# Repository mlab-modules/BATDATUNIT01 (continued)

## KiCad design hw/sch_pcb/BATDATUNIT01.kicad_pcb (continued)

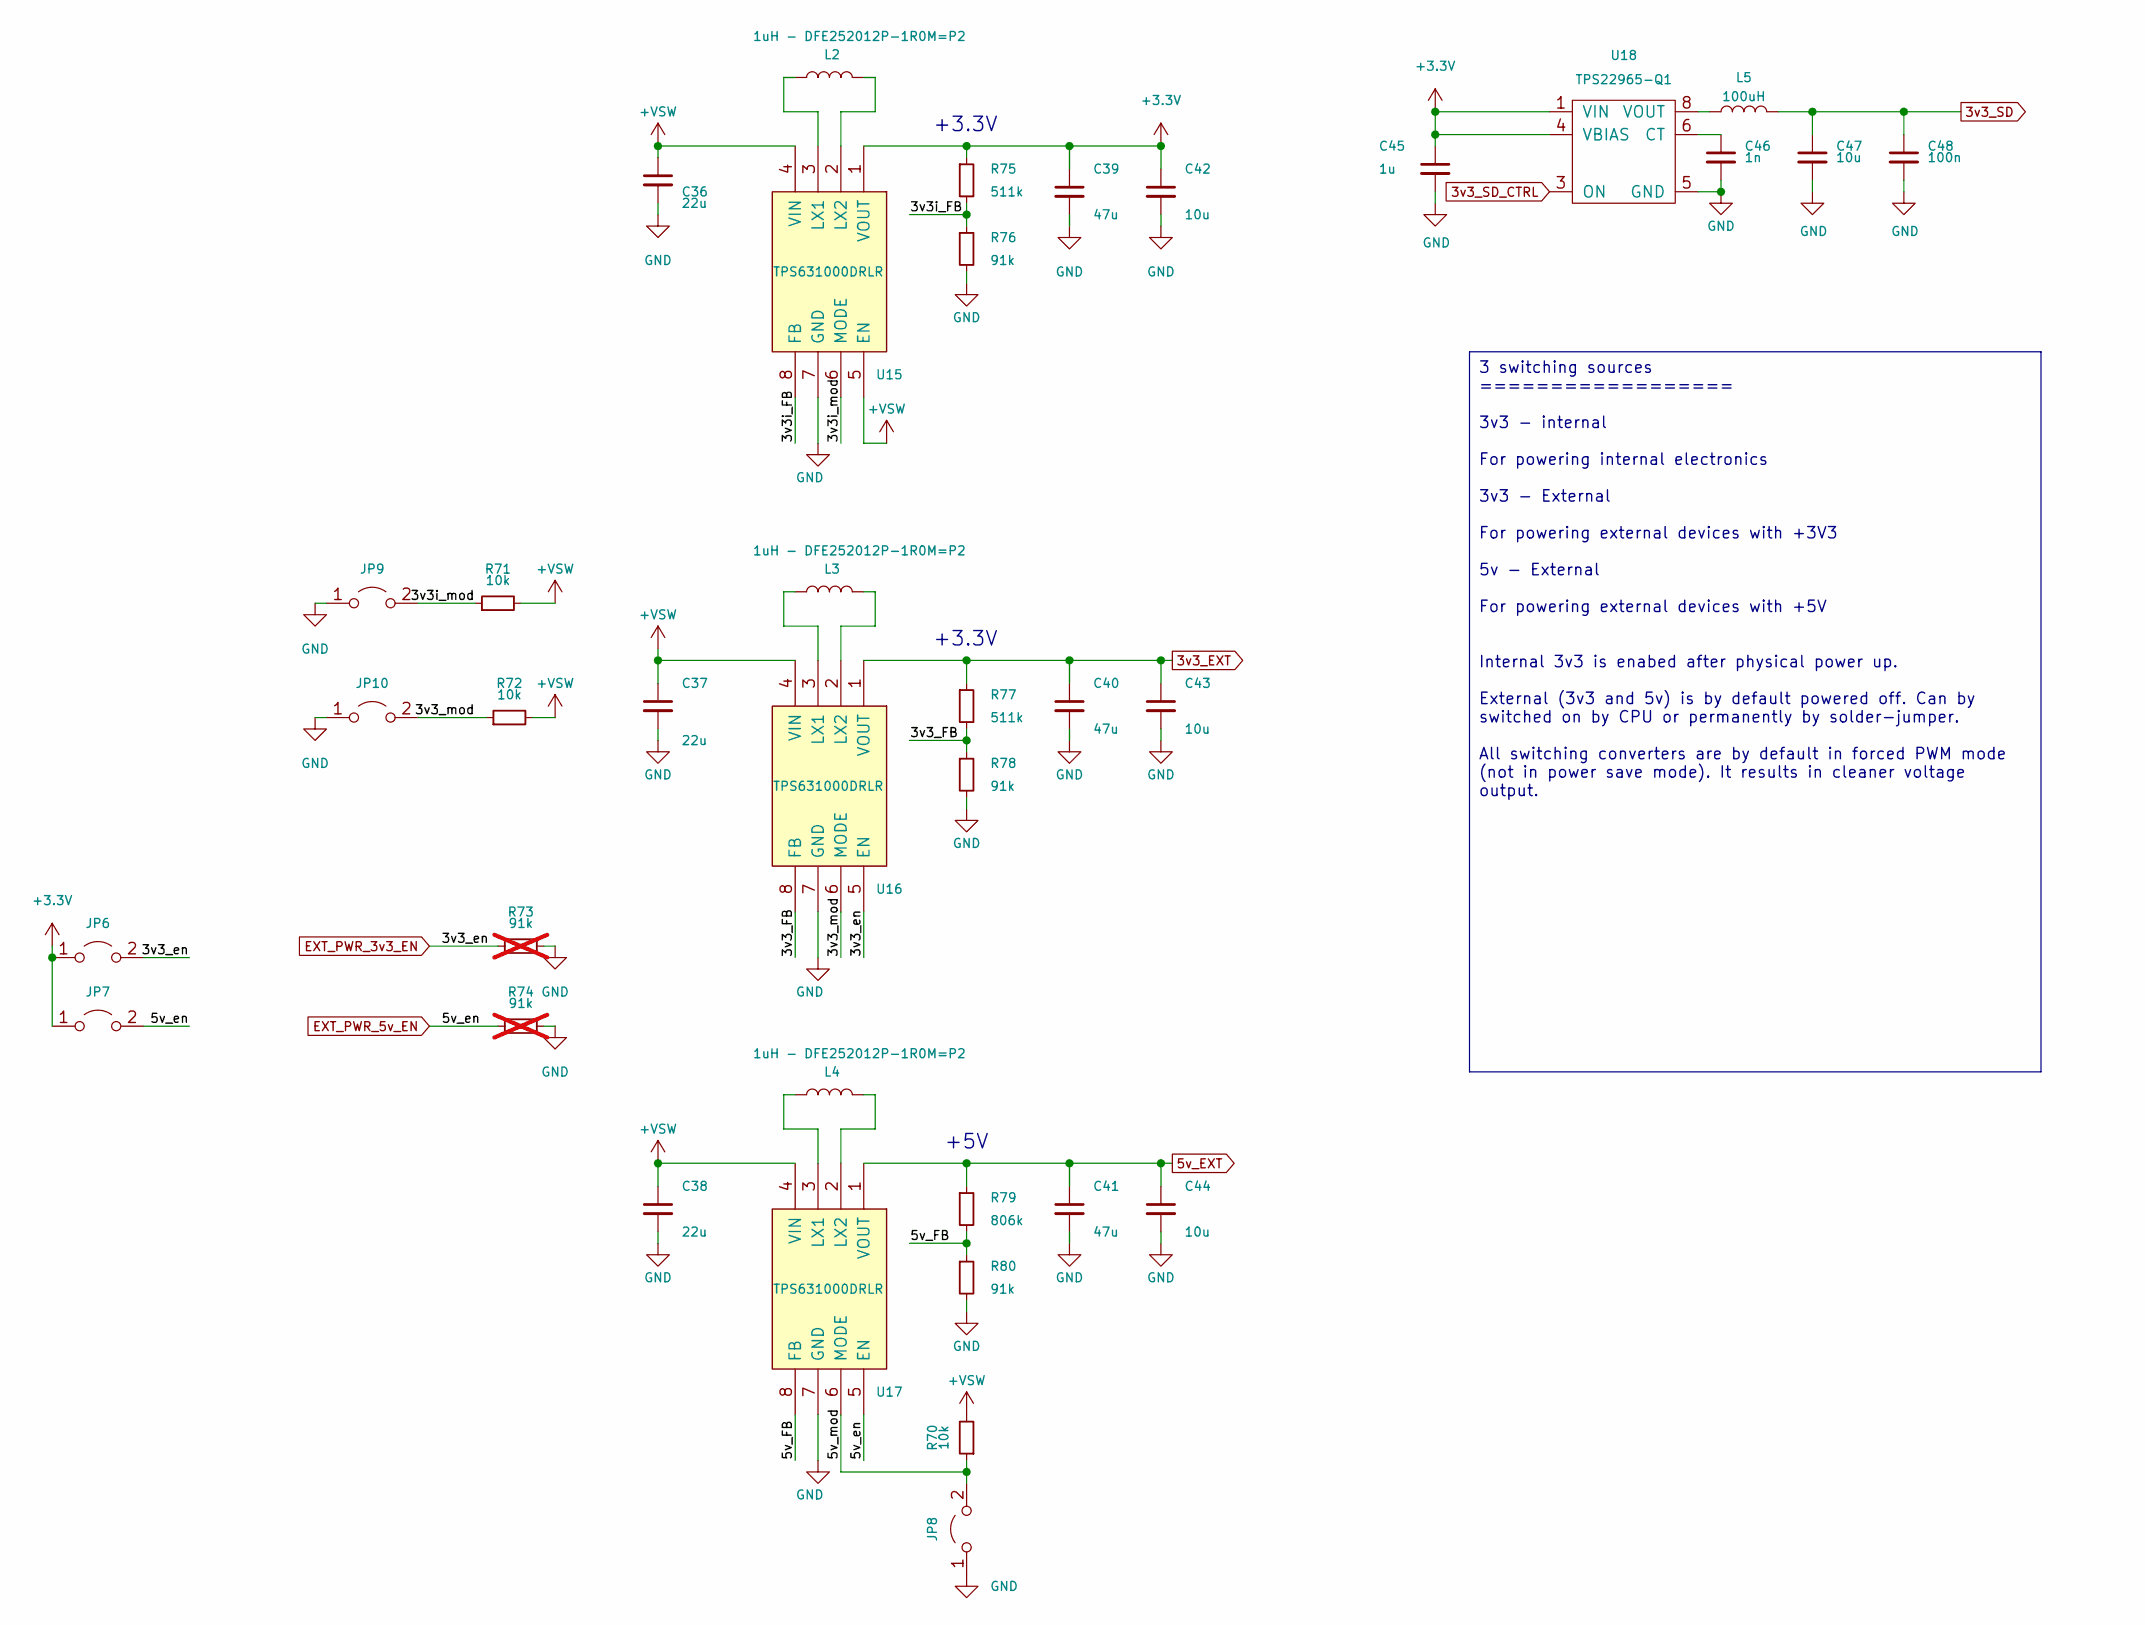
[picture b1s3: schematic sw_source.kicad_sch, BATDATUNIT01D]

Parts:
C36, C37, C38: 22u; C_0805_2012Metric
C39, C40, C41: 47u; C_0805_2012Metric
C42, C43, C44, C47: 10u; C_0805_2012Metric
C45: 1u; C_0805_2012Metric
C46: 1n; C_0805_2012Metric
C48: 100n; C_0805_2012Metric
JP6, JP7, JP8, JP9, JP10: Jumper_2_Open; SolderJumper-2_P1.3mm_Open_RoundedPad1.0x1.5mm
L2, L3, L4: 1uH - DFE252012P-1R0M=P2; L_1008_2520Metric
L5: 100uH; L_0805_2012Metric_Pad1.15x1.40mm_HandSolder
R70, R71, R72: 10k; R_0805_2012Metric
R73, R74: 91k; R_0805_2012Metric; not fitted
R75, R77: 511k; R_0805_2012Metric
R76, R78, R80: 91k; R_0805_2012Metric
R79: 806k; R_0805_2012Metric
U15, U16, U17: TPS631000DRLR; SOT-583-8; Mouser Part Number 595-TPS631000DRLR
U18: TPS22965-Q1; WSON-8-1EP_2x2mm_P0.5mm_EP0.9x1.6mm

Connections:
3v3_EXT: C40.1, C43.1, R77.1, U16.1 (VOUT); also elsewhere on the board
3v3_SD: C47.1, C48.1, L5.2; also elsewhere on the board
3v3_SD_CTRL: U18.3 (ON); also elsewhere on the board
5v_EXT: C41.1, C44.1, R79.1, U17.1 (VOUT); also elsewhere on the board
+3.3V: C39.1, C42.1, C45.1, JP6.1 (A), JP7.1 (A), R75.1, U15.1 (VOUT), U18.1 (VIN), U18.2 (VIN), U18.4 (VBIAS); also elsewhere on the board
+VSW: C36.1, C37.1, C38.1, R70.2, R71.2, R72.2, U15.4 (VIN), U15.5 (EN), U16.4 (VIN), U17.4 (VIN); also elsewhere on the board
/sw_source/3v3_FB: R77.2, R78.1, U16.8 (FB)
/sw_source/3v3_mod: JP10.2 (B), R72.1, U16.6 (MODE)
/sw_source/3v3i_FB: R75.2, R76.1, U15.8 (FB)
/sw_source/3v3i_mod: JP9.2 (B), R71.1, U15.6 (MODE)
/sw_source/5v_FB: R79.2, R80.1, U17.8 (FB)
/sw_source/5v_mod: JP8.2 (B), R70.1, U17.6 (MODE)
EXT_PWR_3v3_EN: JP6.2 (B), R73.2, U16.5 (EN); also elsewhere on the board
EXT_PWR_5v_EN: JP7.2 (B), R74.2, U17.5 (EN); also elsewhere on the board
GND: C36.2, C37.2, C38.2, C39.2, C40.2, C41.2, C42.2, C43.2, C44.2, C45.2, C46.2, C47.2, C48.2, JP8.1 (A), JP9.1 (A), JP10.1 (A), R73.1, R74.1, R76.2, R78.2, R80.2, U15.7 (GND), U16.7 (GND), U17.7 (GND), U18.5 (GND), U18.9; also elsewhere on the board
unnamed: L5.1, U18.7 (VOUT), U18.8 (VOUT)
unnamed: L2.1, U15.3 (LX1)
unnamed: L2.2, U15.2 (LX2)
unnamed: L3.1, U16.3 (LX1)
unnamed: L3.2, U16.2 (LX2)
unnamed: L4.1, U17.3 (LX1)
unnamed: L4.2, U17.2 (LX2)
unnamed: C46.1, U18.6 (CT)

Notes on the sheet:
+3.3V
+5V
3 switching sources ================== 3v3 - internal For powering internal electronics 3v3 - External For powering external devices with +3V3 5v - External For powering external devices with +5V Internal 3v3 is enabed after physical power up. External (3v3 and 5v) is by default powered off. Can by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

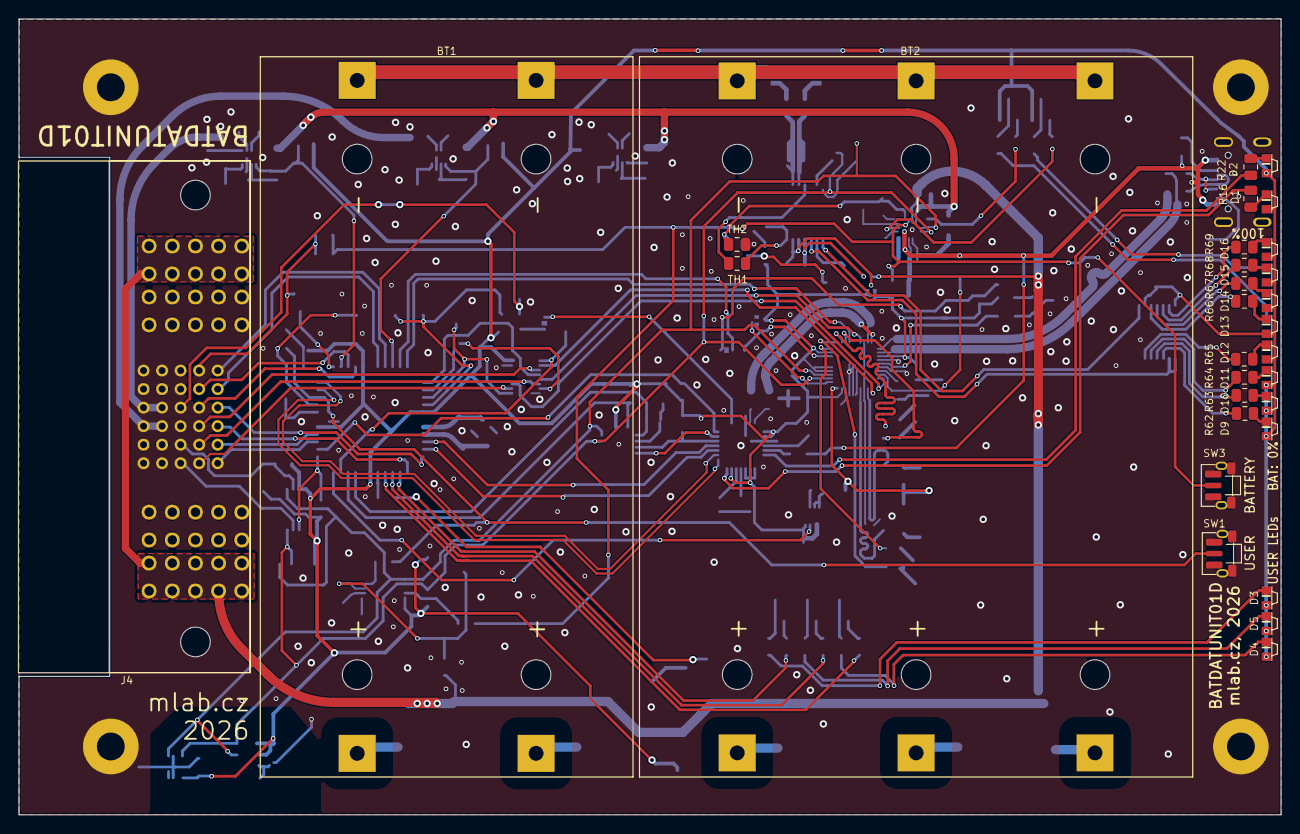
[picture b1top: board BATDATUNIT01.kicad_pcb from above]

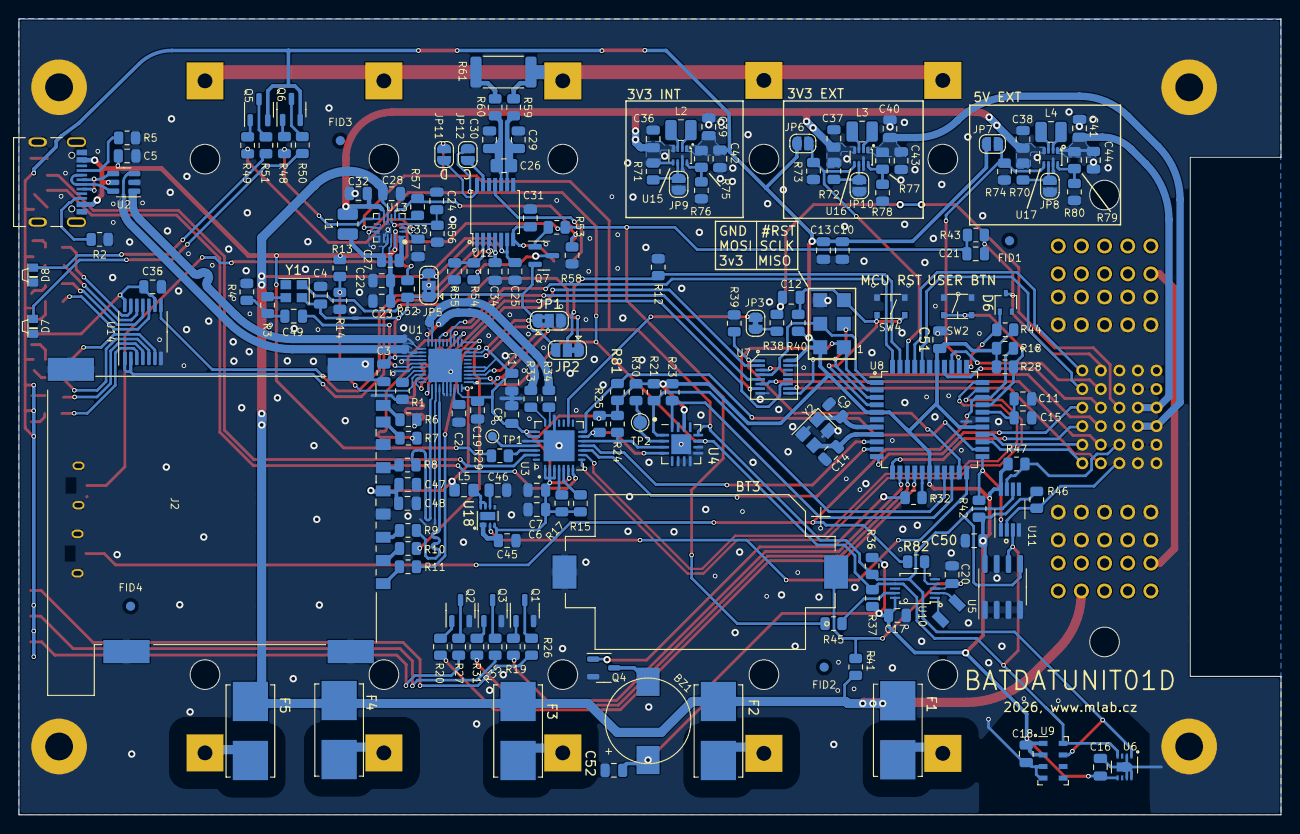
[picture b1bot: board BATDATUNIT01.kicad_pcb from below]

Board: 2 copper layers, 136.2 x 85.9 mm, 225 parts (191 on the bottom side), 182 nets.

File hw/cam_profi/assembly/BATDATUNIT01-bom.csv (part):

Component,Description,Part,References,Value,Footprint,Quantity Per PCB,Datasheet,ust_id,mfpn,mpn,sim.device,sim.type,sim.pins,height,i2c,manufacturer_name,manufacturer_part_number,mouser part number,mouser price/stock,arrow part number,arrow price/stock,lcsc
1,Single-cell battery,2xBATT,BT1,BATT,BAT_BK-18650-PC4,1,~,5c70984412875079b91f87e9,,,,,,,,,,,,,,
2,Single-cell battery,3xBATT,BT2,BATT,BAT_BK-18650-PC6,1,~,63567f66c8e7b5bbef872ce1,,,,,,,,,,,,,,
3,Single-cell battery,Battery_Cell,BT3,CR2032,BatteryHolder_Keystone_1060_1x2032,1,~,68249eacee7fc534862c6977,,,,,,,,,,,,,,
4,"Buzzer, polarized",Buzzer,BZ1,LET9032ES-03L,MagneticBuzzer_LET9032ES-03L-2.7-16-R,1,https://www.cre-soundbuzzer.com/datasheet/LET9032ES-03L-2.7-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,5fa0f13812875025b3977890,,,,,,,,,,,,,,
5,"Unpolarized capacitor, small symbol",C_Small,C9C14,15p,C_0805_2012Metric,2,~,5c70984712875079b91f8b32,,,,,,,,,,,,,,
6,"Unpolarized capacitor, small symbol",C_Small,C5C46,1n,C_0805_2012Metric,2,~,5c70984712875079b91f8b45,C0805 1u,C0805 1u,,,,,,,,,,,,
7,"Unpolarized capacitor, small symbol",C_Small,C34,3n3,C_0805_2012Metric,1,~,5c70984712875079b91f8b47,,,,,,,,,,,,,,
8,"Unpolarized capacitor, small symbol",C_Small,C27,47n,C_0805_2012Metric,1,~,65482046462c6d9e72056b98,,,,,,,,,,,,,,
9,"Unpolarized capacitor, small symbol",C_Small,C1C2C3C4C6C8C10C13C15C16C17C18C20C23C25C26C29C30C35C48C49C50C51C52,100n,C_0805_2012Metric,24,~,5c70984712875079b91f8b4c,,,,,,,,,,,,,,
10,"Unpolarized capacitor, small symbol",C_Small,C19C24C31C45,1u,C_0805_2012Metric,4,~,5c70984712875079b91f8b50,,,,,,,,,,,,,,
11,"Unpolarized capacitor, small symbol",C_Small,C7C12C33,4u7,C_0805_2012Metric,3,~,5c70984712875079b91f8b52,,,,,,,,,,,,,,
12,"Unpolarized capacitor, small symbol",C_Small,C11C22C28C42C43C44C47,10u,C_0805_2012Metric,7,~,5c70984712875079b91f8b53,,,,,,,,,,,,,,
13,"Unpolarized capacitor, small symbol",C_Small,C21C32C36C37C38,22u,C_0805_2012Metric,5,~,650b58f1462c6d9e7205463b,,,,,,,,,,,,,,
14,"Unpolarized capacitor, small symbol",C_Small,C39C40C41,47u,C_0805_2012Metric,3,~,5c70984812875079b91f8bbf,,,,,,,,,,,,,,
15,"100V, 0.175A, High-speed Switching Diode, SOT-323",BAS16W,D6,BAS16W,SOT-323_SC-70,1,https://assets.nexperia.com/documents/data-sheet/BAS16_SER.pdf,5c70984512875079b91f88af,,,,,,,,,,,,,,
16,"Light emitting diode, small symbol",LED_Small,D3D8D13D14D15D16,GREEN,SMD_LED_RIGHT_KINGBRIGHT_1605,6,~,65481f0c462c6d9e72056b3d,,,,,,,,,,,,,,
17,Light emitting diode,LED,D2,GREEN,SMD_LED_RIGHT_KINGBRIGHT_1605,1,https://cz.mouser.com/datasheet/2/216/APA1606SGC-76546.pdf,65481f0c462c6d9e72056b3d,,,,,,,,,,,,,,
18,"Light emitting diode, small symbol",LED_Small,D4D7D11D12,ORANGE,SMD_LED_RIGHT_KINGBRIGHT_1605,4,~,65481fdd462c6d9e72056b6a,,,,,,,,,,,,,,
19,Light emitting diode,LED,D1,RED,SMD_LED_RIGHT_KINGBRIGHT_1605,1,https://cz.mouser.com/datasheet/2/216/APA1606SURCK-63848.pdf,65481f96462c6d9e72056b54,,,,,,,,,,,,,,
20,"Light emitting diode, small symbol",LED_Small,D5D9D10,RED,SMD_LED_RIGHT_KINGBRIGHT_1605,3,~,65481f96462c6d9e72056b54,,,,,,,,,,,,,,
21,Fuse,Fuse,F1F2F3F4F5,Fuse,Fuseholder_Littelfuse_Nano2_154x,5,https://cz.mouser.com/datasheet/2/240/media-3321028.pdf,5c70984512875079b91f88d8,,,,,,,,,,,,,,
22,,MOLEX_46436-9327,J4,46436-9327,MOLEX_46436-9327,1,,65481d4a462c6d9e72056b06,,,,,,,,,,,,,,
23,2x03 2.54 mm pitch header,HEADER_2x03,J3,HEADER_2x03,SMD_2x03,1,,x,,,,,,,,,,,,,,
24,,SD_Card-FPS009-4200-0,J2,SD_Card-FPS009-4200-0,FPS009-4200-0,1,,5cdd24d5128750448edda353,,,,,,,,,,,,,,
25,USB 2.0-only Type-C Receptacle connector,USBC_USB4105-GF-A,J1,USBC_USB4105-GF-A,USBC GCT_USB4105-GF-A,1,,5fa0f94612875025b397795e,USB4105-GF-A,USB4105-GF-A,,,,,,,,,,,,
26,"Jumper, 2-pole, open",Jumper_2_Open,JP6JP7JP8JP9JP10JP11JP12,Jumper_2_Open,SolderJumper-2_P1.3mm_Open_RoundedPad1.0x1.5mm,7,~,x,,,,,,,,,,,,,,
27,Inductor,L,L5,100uH,L_0805_2012Metric_Pad1.15x1.40mm_HandSolder,1,~,626fd6fcdc56076e9a222966,,,,,,,,,,,,,,
28,Inductor,L,L1L2L3L4,1uH - DFE252012P-1R0M=P2,L_1008_2520Metric,4,~,650b5977462c6d9e72054656,,,,,,,,,,,,,,
29,"PNP transistor, base/emitter/collector",Q_PNP_BEC,Q5Q6,BC807-25,SOT-23-3,2,~,5c70984712875079b91f8aeb,,,NPN,GUMMELPOON,1=C 2=B 3=E,,,,,,,,,
30,"NPN transistor, base/emitter/collector",Q_NPN_BEC,Q1Q2Q3Q4,BC817-25,SOT-23-3,4,~,5c70984712875079b91f8aea,,,NPN,GUMMELPOON,1=C 2=B 3=E,,,,,,,,,
31,"P-MOSFET transistor, gate/source/drain",Q_PMOS_GSD,Q7,BSS83P,SOT-23,1,~,5c70984712875079b91f8ae6,,,,,,,,,,,,,,
32,"Resistor, small symbol",R_Small,R33R34,33R,R_0805_2012Metric,2,~,5c70984512875079b91f8970,,,,,,,,,,,,,,
33,"Resistor, small symbol",R_Small,R22R26R51R66R67R68R69,68R,R_0805_2012Metric,7,~,5c70984512875079b91f8975,,,,,,,,,,,,,,
34,,R-device-DATALOGGER01A-rescue-CCP2019V01A-rescue-SPACEDOS01A_PCB01A-rescue-SPACEDOS01B_PCB01A-rescue,R6R7R8R9R10R11R38R82,100R,R_0805_2012Metric,8,,5c70984512875079b91f8977,,,,,,,,,,,,,,
35,"Resistor, small symbol",R_Small,R59R60,100R,R_0805_2012Metric,2,~,5c70984512875079b91f8977,,,,,,,,,,,,,,
36,"Resistor, small symbol",R_Small,R16R27R35R50R54R62R63R64R65,270R,R_0805_2012Metric,9,~,5c70984512875079b91f8983,,,,,,,,,,,,,,
37,"Resistor, small symbol",R_Small,R53,510R,R_0805_2012Metric,1,~,5c70984512875079b91f8988,,,,,,,,,,,,,,
38,"Resistor, small symbol",R_Small,R15R17R19R20R31R32R48R49R55,1k,R_0805_2012Metric,9,~,5c70984512875079b91f898c,,,,,,,,,,,,,,
39,"Resistor, small symbol",R_Small,R56,2k4,R_0805_2012Metric,1,~,5c70984612875079b91f8991,,,,,,,,,,,,,,
40,"Resistor, small symbol",R_Small,R2R4R5R29R57,5k1,R_0805_2012Metric,5,~,5fa0fc3e12875025b3977997,,,,,,,,,,,,,,
41,"Resistor, small symbol",R_Small,R1,6.19k,R_0805_2012Metric,1,~,6548142e462c6d9e72056976,,,,,,,,,,,,,,
42,"Resistor, small symbol",R_Small,R3R18R21R23R24R25R28R30R36R37R40R42R44R46R47R70R72R81,10k,R_0805_2012Metric,18,~,5c70984612875079b91f899f,,,,,,,,,,,,,,
43,"Resistor, small symbol",R_Small,R14,25k5,R_0805_2012Metric,1,~,5c70984712875079b91f8a88,,,,,,,,,,,,,,
44,"Resistor, small symbol",R_Small,R58,33k,R_0805_2012Metric,1,~,5c70984712875079b91f8a8a,,,,,,,,,,,,,,
45,"Resistor, small symbol",R_Small,R13,68k,R_0805_2012Metric,1,~,5c70984712875079b91f8a91,,,,,,,,,,,,,,
46,"Resistor, small symbol",R_Small,R76R78R80,91k,R_0805_2012Metric,3,~,5c70984712875079b91f8a95,,,,,,,,,,,,,,
47,"Resistor, small symbol",R_Small,R43,270k,R_0805_2012Metric,1,~,5c70984712875079b91f8aa0,,,,,,,,,,,,,,
48,"Resistor, small symbol",R_Small,R75R77,511k,R_0805_2012Metric,2,~,650b5a43462c6d9e7205468e,,,,,,,,,,,,,,
49,"Resistor, small symbol",R_Small,R79,806k,R_0805_2012Metric,1,~,650b5abb462c6d9e720546b8,,,,,,,,,,,,,,
50,"Resistor, small symbol",R_Small,R61,0R01 75PPM,R_2512_6332Metric,1,~,5c70984712875079b91f8abf,,,,,,,,,,,,,,
51,"Push button switch, generic, two pins",SW_Push,SW2SW4,KMT031,KMT031 NGJ LHS C&K,2,~,612515a61287500165a9771d,,,,,,,,,,,,,,
52,"Push button switch, generic, two pins",SW_Push_shield,SW1SW3,SKRTLAE010,SKRT,2,~,65481517462c6d9e720569b4,,,,,,,,,,,,,,
53,Temperature dependent resistor,Thermistor,TH1,10k NTC,R_0805_2012Metric,1,~,5c70984712875079b91f8ac5,,,,,,,,,,,,,,
54,"Temperature dependent resistor, negative temperature coefficient",Thermistor_NTC,TH2,10k NTC,R_0805_2012Metric,1,~,5c70984712875079b91f8ac5,,,,,,,,,,,,,,
55,"I2C Serial EEPROM, 64Kb (8192x8) with Unique Serial Number, SO8",AT24CS64-SSHM,U5,AT24CS64-SSHM,SOIC-8_3.9x4.9mm_P1.27mm,1,http://ww1.microchip.com/downloads/en/DeviceDoc/Atmel-8870-S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,5c70984712875079b91f8b99,,,,,,1.5,,,,,,,,
56,"20MHz, 128kB Flash, 16kB SRAM, 4kB EEPROM, JTAG, TQFP-44",ATmega1284P-A,U8,ATMEGA1284P-AU,TQFP-44_10x10mm_P0.8mm,1,http://www.atmel.com/Images/Atmel-8272-8-bit-AVR-microcontro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,5c70984412875079b91f888e,,,,,,1.1,,,,,,,,
57,"BQ25628E I2C Controlled 1-Cell, 2-A, Maximum 18-V Input, Buck Battery Charger with
NVDC Power Path Management",BQ25628E,U13,BQ25628E,Texas_S-WQFN-HR-18,1,https://www.ti.com/lit/ds/symlink/bq25628e.pdf,65481a71462c6d9e72056aa4,,,,,,,0x6B,,,,,,,
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
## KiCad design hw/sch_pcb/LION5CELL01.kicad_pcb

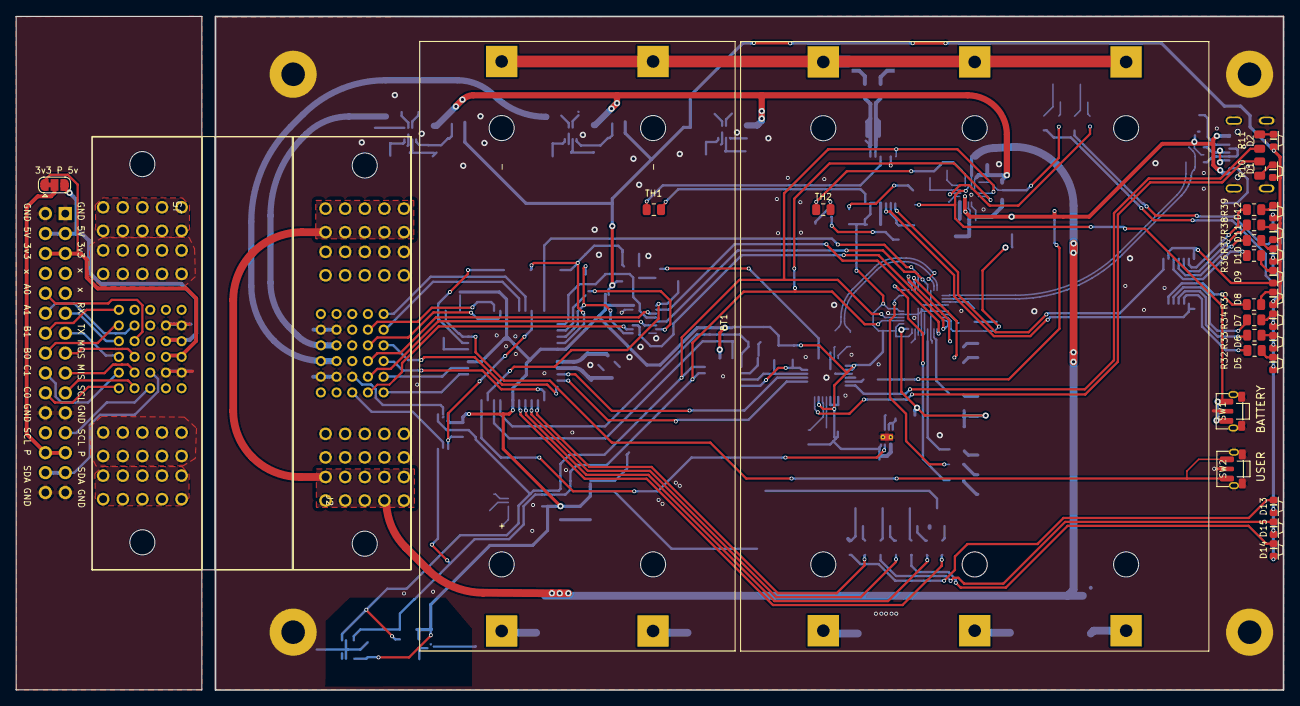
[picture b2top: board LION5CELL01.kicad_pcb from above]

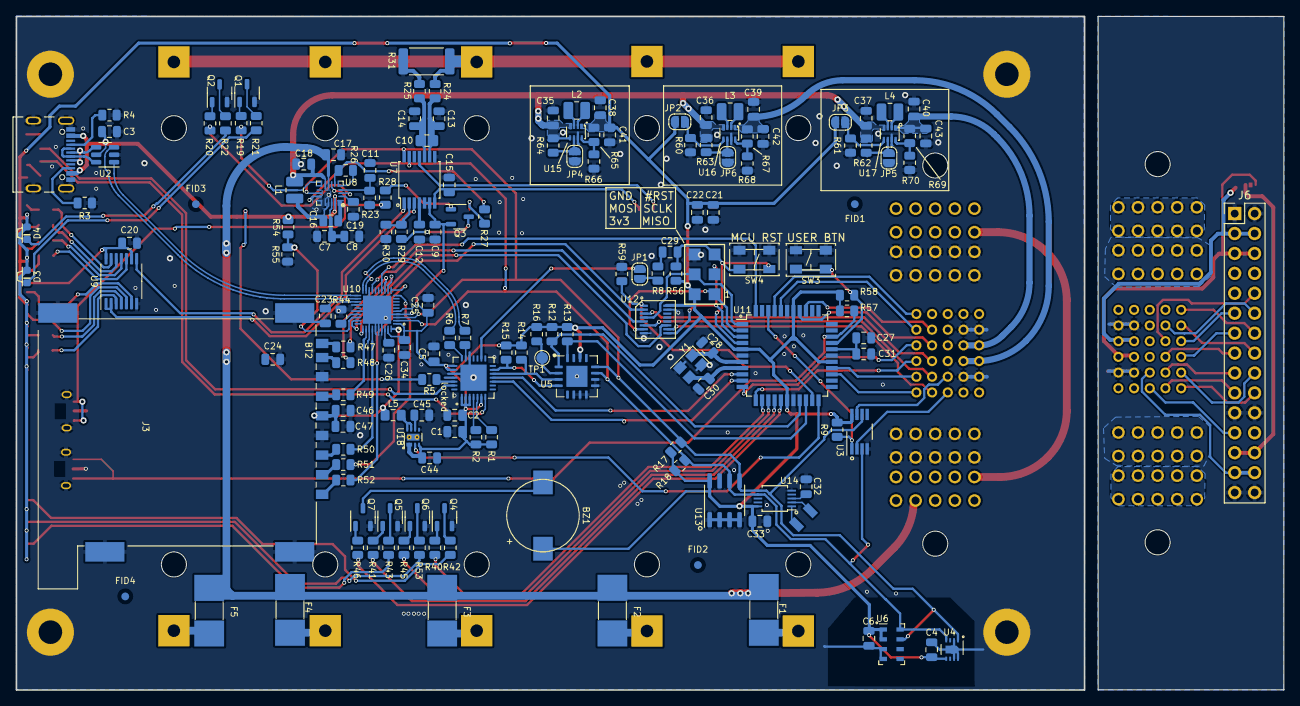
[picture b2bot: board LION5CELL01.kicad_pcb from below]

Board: 2 copper layers, 161.6 x 85.9 mm, 202 parts (166 on the bottom side), 184 nets.

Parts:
BT1: BATT; BAT_BK-18650-PC4
BT2: BATT; BAT_BK-18650-PC6
BZ1: LET9032ES-03L-2.7-16-R; MagneticBuzzer_LET9032ES-03L-2.7-16-R
C1, C4, C5, C6, C8, C9, C10, C13, C14, C20, C21, C22, C23, C25, C26, C31, C32, C33, C47: 100n; C_0805_2012Metric
C2, C19, C29: 4u7; C_0805_2012Metric
C3: 1n; C_0805_2012Metric
C7, C11, C17: 10u; C_0805_2012Metric
C12: 3n3; C_0805_2012Metric
C15, C34, C44: 1u; C_0805_2012Metric
C16: 47n; C_0805_2012Metric
C18: 20u; C_0805_2012Metric
C24: C_Small; C_0805_2012Metric
C27, C41, C42, C43, C46: 10uF; C_0805_2012Metric
C28, C30: 15pF; C_0805_2012Metric
C35, C36, C37: 22uF; C_0805_2012Metric
C38, C39, C40: 47uF; C_0805_2012Metric
C45: 1nF; C_0805_2012Metric
D1, D11, D12: RED; SMD_LED_RIGHT_KINGBRIGHT_1605
D2, D4, D5, D6, D7, D8: GREEN; SMD_LED_RIGHT_KINGBRIGHT_1605
D3, D13, D14, D15: ORANGE; SMD_LED_RIGHT_KINGBRIGHT_1605
D9, D10: ORAGE; SMD_LED_RIGHT_KINGBRIGHT_1605
F1, F2, F3, F4, F5: Fuse; Drzak_2410
FID1, FID2, FID3, FID4: Fiducial; Fiducial_1mm_Mask2mm
H1, H2, H3, H4: M3; MountingHole_3mm
J1: USBC_USB4105-GF-A; USBC GCT_USB4105-GF-A
J2: 46436-9327; MOLEX_46436-9327
J3: SD_Card-FPS009-4200-0; FPS009-4200-0
J4: HEADER_2x03; SMD_2x03
J5: 46436-9327; MOLEX_46437-9327
J6: HEADER_2x15; PinHeader_2x15_P2.54mm_Vertical
JP1: SolderJumper_2_Open; SolderJumper-2_P1.3mm_Open_RoundedPad1.0x1.5mm
JP2, JP3, JP4, JP5, JP6: Jumper_2_Open; SolderJumper-2_P1.3mm_Open_RoundedPad1.0x1.5mm
JP7: Jumper_3_Bridged12; SolderJumper-3_P1.3mm_Bridged12_RoundedPad1.0x1.5mm
L1, L2, L3, L4: 1uH - DFE252012P-1R0M=P2; L_1008_2520Metric
L5: 100uH; L_0805_2012Metric_Pad1.15x1.40mm_HandSolder
NT1, NT2: NetTie_2; NetTie-2_SMD_Pad0.5mm
Q1, Q2, Q4, Q5, Q6, Q7: BC817-25; SOT-23-3
Q3: BC807-25; SOT-23-3
R1, R2, R12, R13, R14, R15, R16, R17, R18, R19, R20, R30, R40, R41, R45, R46, R54, R55, R60, R61, R62, R63, R64: 1k; R_0805_2012Metric
R3, R4, R57, R58: R_Small; R_0805_2012Metric
R5: 5k1 (cca); R_0805_2012Metric
R6, R7: 33R; R_0805_2012Metric
R8, R24, R25, R47, R48, R49, R50, R51, R52: 100R; R_0805_2012Metric
R9, R56, R59: 10k; R_0805_2012Metric
R10, R11, R21, R22, R23, R26, R27, R42, R43, R53: R; R_0805_2012Metric
R28: 500R; R_0805_2012Metric
R29: 250R; R_0805_2012Metric
R31: 0R01 75PPM; R_2512_6332Metric
R32, R33, R34, R35, R36, R37, R38, R39: 270R; R_0805_2012Metric
R44: 6.19k; R_0805_2012Metric
R65, R67: 511k; R_0805_2012Metric
R66, R68, R70: 91k; R_0805_2012Metric
R69: 806k; R_0805_2012Metric
SW1, SW2: SKRTLAE010; SKRT
SW3, SW4: KMT031; KMT031 NGJ LHS C&K
TH1, TH2: 10k NTC; R_0805_2012Metric
TP1: MUX_RST; TestPoint_Pad_D1.5mm
U2: USBLC6-2SC6; SOT-23-6
U3: TCA4307; VSSOP-8_3.0x3.0mm_P0.65mm
U4: SHT35-DIS; Sensirion_DFN-8-1EP_2.5x2.5mm_P0.5mm_EP1.1x1.7mm
U5: PCA9541ABS/01; QFN-16-1EP_5x5mm_P0.8mm_EP2.7x2.7mm
U6: MS561101BA03-50; LGA-8_3x5mm_P1.25mm
U7: BQ34Z100; TSSOP-14_4.4x5mm_Pitch0.65mm
U8: BQ25628E; Texas_S-WQFN-HR-18
U9: SN74HC164D; TSSOP-14_4.4x5mm_P0.65mm
U10: MAX14502AETL+; QFN40P500X500X80-41N
U11: ATMEGA1284P-AU; TQFP-44_10x10mm_P0.8mm
U12: TMUX1574DYYR; SOT-23-16 THIN
U13: AT24CS64-SSHM; SOIC-8_3.9x4.9mm_P1.27mm
U14: PCF85263A; TSSOP-10_3x3mm_P0.5mm
U15, U16, U17: TPS631000DRLR; SOT-583-8
U18: TPS22965-Q1; WSON-8-1EP_2x2mm_P0.5mm_EP0.9x1.6mm_ThermalVias
Y1: 8 MHz; Crystal_SMD_3225-4Pin_3.2x2.5mm
Y2: ABS07-120-32.768KHZ-T; ABS07
locked: FT260Q-T; QFN-28-1EP_5x5mm_P0.5mm_EP3.35x3.35mm

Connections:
3v3_EXT: C39.1, C42.1, J2.A3, J2.B3, R67.1, U16.1 (VOUT)
3v3_SD: C46.1, C47.1, J3.4 (VDD), L5.2, U10.40 (VSD)
3v3_SD_CTRL: U11.22 ((PCINT19/TMS)PC3), U18.3 (ON)
5v_EXT: C40.1, C43.1, J2.A4, J2.B4, R69.1, U17.1 (VOUT)
+3.3V: BZ1.1 (-), C1.1, C2.1, C4.1, C5.1, C6.1, C9.1, C20.1, C21.1, C22.1, C25.1, C33.1, C34.1, C38.1, C41.1, C44.1, D1.2 (A), D2.2 (A), D3.2 (A), D4.2 (A), D5.2 (A), D6.2 (A), D7.2 (A), D8.2 (A), D9.2 (A), D10.2 (A), D11.2 (A), D12.2 (A), D13.2 (A), D14.2 (A), D15.2 (A), J4.2, JP2.1 (A), JP3.1 (A), Q3.2 (E), R1.1, R2.1, R9.2, R12.2, R13.2, R14.2, R15.2, R16.2, R17.2, R18.2, R56.2, R57.1, R58.1, R65.1, U3.8 (VCC), U4.5 (VDD), U5.14 (VDD), U6.1 (VDD), U6.2 (PS), U7.5 (CE), U7.6 (REGIN), U9.9 (CLR), U9.14 (VCC), U10.1 (I2C_SEL), U10.5 (VIO), U10.39 (VCC), U11.5 (VCC), U11.17 (VCC), U11.27 (AVCC), U11.38 (VCC), U12.16 (VDD), U13.8 (VCC), U14.10 (VDD), U15.1 (VOUT), U18.1 (VIN), U18.2 (VIN), U18.4 (VBIAS), locked.1 (DEBUGGER), locked.2 (STEST_RSTN), locked.3 (RESETN), locked.6 (VCCIO), locked.22 (VOUT3V3), locked.23 (VCCIN)
+BATT: C17.1, F1.1, F2.1, F3.1, F4.1, F5.1, J2.P1, J2.P4, U8.8 (BAT)
+VSW: C18.1, C35.1, C36.1, C37.1, L1.2, R62.2, R63.2, R64.2, U8.9 (SYS), U15.4 (VIN), U15.5 (EN), U16.4 (VIN), U17.4 (VIN)
/D+: J1.A6 (D+), J1.B6 (D+), U2.4 (I/O2)
/D-: J1.A7 (D-), J1.B7 (D-), U2.6 (I/O1)
/DTR: JP1.2 (B), locked.16 (DIO9)
/External_connector/3v3: J5.A3, J5.B3, J6.5, J6.6, JP7.1 (A)
/External_connector/5v: J5.A4, J5.B4, J6.3, J6.4, JP7.3 (B)
/External_connector/A0: J5.D4, J6.10
/External_connector/A1: J5.D5, J6.12
/External_connector/B0: J5.E5, J6.16
/External_connector/B1: J5.E6, J6.14
/External_connector/BATT: J5.P1, J5.P4
/External_connector/C0: J5.E1, J6.20
/External_connector/C1: J5.E2, J6.18
/External_connector/I2C_PWR: J6.25, J6.26, JP7.2 (C)
/External_connector/MISO: J5.D2, J6.17
/External_connector/MOSI: J5.D3, J6.15
/External_connector/RX: J5.E4, J6.11
/External_connector/SCL: J5.C1, J6.23, J6.24
/External_connector/SCLK: J5.D1, J6.19
/External_connector/SDA: J5.C2, J6.27, J6.28
/External_connector/TX: J5.E3, J6.13
/MCU_RXD: U11.9 ((PCINT24/RXD0)PD0), locked.11 (DIO4)
/MCU_TXD: U11.10 ((PCINT25/TXD0)PD1), locked.10 (DIO3)
/SCL_USB: R14.1, U5.3 (SCL_MST1), locked.12 (DIO5)
/SDA_USB: R15.1, U5.4 (SDA_MST1), locked.13 (DIO6)
/UART_RX_LED: R11.2, locked.27 (DIO12)
/UART_TX_LED: R10.2, locked.7 (DIO0)
/liion/A: R32.2, U9.3 (QA)
/liion/B: R33.2, U9.4 (QB)
/liion/Battery+: C12.1, U7.4 (BAT)
/liion/C: R34.2, U9.5 (QC)
/liion/CH_BTN: R28.1, SW1.1, U8.7 (~QON)
/liion/CH_PG: R20.1, U8.3 (~PG)
/liion/CH_STAT: R19.1, U8.10 (STAT)
/liion/D: R35.2, U9.6 (QD)
/liion/E: R36.2, U9.10 (QE)
/liion/F: R37.2, U9.11 (QF)
/liion/G: R38.2, U9.12 (QG)
/liion/GAUGE_BTN_IN: R29.1, R30.2, U7.2 (VEN)
/liion/GAUGE_SRN: NT2.1, R25.1
/liion/GAUGE_SRP: NT1.1, R24.1
/liion/H: R39.2, U9.13 (QH)
/liion/P1: U7.3 (P1), U9.1 (A), U9.2 (B)
/liion/P2: U7.1 (P2), U9.8 (CLK)
/mcu/BTN_USER_A: R57.2, SW2.1, U11.31 ((PCINT6/ADC6)PA6)
/mcu/BTN_USER_B: R58.2, SW3.1, U11.30 ((PCINT7/ADC7)PA7)
/mcu/CCLK: R49.1, U10.32 (CCLK1)
/mcu/CCMD: R50.1, U10.34 (CCMD1)
/mcu/CDAT0: R48.2, U10.13 (CDAT1_0)
/mcu/CDAT1: R47.2, U10.12 (CDAT1_1)
/mcu/CDAT2: R52.1, U10.11 (CDAT1_2)
/mcu/CDAT3: R51.1, U10.10 (CDAT1_3)
/mcu/CLDO: C26.1, U10.38 (CLDO)
/mcu/CS_SD: U10.14 (HDAT1_3), U11.44 ((PCINT12/OC0B/~SS)PB4)
/mcu/LED_U1: R40.1, U11.13 ((PCINT28/XCK1/OC1B)PD4)
/mcu/LED_U2: R45.1, U11.14 ((PCINT294/OC1A)PD5)
/mcu/LED_U3: R41.1, U11.15 ((PCINT30/OC2B/ICP)PD6)
/mcu/MISO_MCU: J4.1, U11.2 ((PCINT14/MISO)PB6), U12.7 (D2)
/mcu/MISO_SD: U10.17 (HDAT1_0), U12.5 (S2A)
/mcu/MOSI_MCU: J4.4, U11.1 ((PCINT13/MOSI)PB5), U12.4 (D1)
/mcu/MOSI_SD: U10.31 (HCMD1), U12.2 (S1A)
/mcu/RREF: R44.1, U10.27 (RREF)
/mcu/RST#_P: C29.1, J4.5, R56.1, SW4.2, U11.4 (~RESET)
/mcu/SCLK_MCU: J4.3, U11.3 ((PCINT15/SCK)PB7), U12.9 (D3)
/mcu/SCLK_SD: U10.29 (HCLK1), U12.11 (S3A)
/mcu/SPI_MUX_SEL: R59.2, U11.21 ((PCINT18/TCK)PC2), U12.1 (SEL)
/mcu/VTM: C23.1, U10.23 (VTM)
/mcu/buzzer: R46.1, U11.16 ((PCINT31/OC2A)PD7)
/sw_source/3v3_FB: R67.2, R68.1, U16.8 (FB)
/sw_source/3v3_mod: JP6.2 (B), R63.1, U16.6 (MODE)
/sw_source/3v3i_FB: R65.2, R66.1, U15.8 (FB)
/sw_source/3v3i_mod: JP4.2 (B), R64.1, U15.6 (MODE)
/sw_source/5v_FB: R69.2, R70.1, U17.8 (FB)
/sw_source/5v_mod: JP5.2 (B), R62.1, U17.6 (MODE)
DET_I2C_EN: R9.1, U3.1 (EN), U11.42 ((PCINT10/AIN0/INT2)PB2)
EXT_A0: J2.D4, U11.37 ((PCINT0/ADC0)PA0)
EXT_A1: J2.D5, U11.36 ((PCINT1/ADC1)PA1)
EXT_B0: J2.E5, U11.40 ((PCINT8/T0/XCK)PB0)
EXT_B1: J2.E6, U11.41 ((PCINT9/CLKO/T1)PB1)
EXT_C0: J2.E1, U11.25 ((PCINT22/TOSC1)PC6)
EXT_C1: J2.E2, U11.26 ((PCINT23/TOSC2)PC7)
EXT_I2C_SCL: J2.C1, U3.2 (SCLout)
EXT_I2C_SDA: J2.C2, U3.7 (SDAout)
EXT_MISO: J2.D2, U12.6 (S2B)
EXT_MOSI: J2.D3, U12.3 (S1B)
EXT_PWR_3v3_EN: JP2.2 (B), R60.2, U16.5 (EN)
EXT_PWR_5v_EN: JP3.2 (B), R61.2, U17.5 (EN)
EXT_RX: J2.E4, U11.11 ((PCINT26/RXD1/INT0)PD2)
EXT_SCLK: J2.D1, U12.10 (S3B)
EXT_TX: J2.E3, U11.12 ((PCINT27/TXD1/INT1)PD3)
GND: C1.2, C2.2, C3.2, C4.2, C5.2, C6.2, C7.2, C8.2, C9.2, C11.2, C12.2, C13.2, C14.2, C15.2, C17.2, C18.2, C19.2, C20.2, C21.2, C22.2, C23.2, C24.2, C25.2, C26.2, C27.2, C28.2, C30.2, C31.2, C32.2, C33.2, C34.2, C35.2, C36.2, C37.2, C38.2, C39.2, C40.2, C41.2, C42.2, C43.2, C44.2, C45.2, C46.2, C47.2, H1.1, H2.1, H3.1, H4.1, J1.A1/B12 (GND), J1.B1/A12 (GND), J1.G1 (SHIELD), J1.G2 (SHIELD), J1.G3 (SHIELD), J1.G4 (SHIELD), J2.A2, J2.A5, J2.B2, J2.B5, J2.P2, J2.P3, J3.3 (VSS), J3.6 (VSS), J3.12 (SHELL1), J4.6, J5.A2, J5.A5, J5.B2, J5.B5, J5.P2, J5.P3, J6.1, J6.2, J6.21, J6.22, J6.29, J6.30, JP4.1 (A), JP5.1 (A), JP6.1 (A), NT2.2, Q1.2 (E), Q2.2 (E), Q4.2 (E), Q5.2 (E), Q6.2 (E), Q7.2 (E), R3.1, R4.1, R23.2, R30.1, R31.2, R44.2, R55.2, R59.1, R60.1, R61.1, R66.2, R68.2, R70.2, SW1.2, SW1.GND (SHIELD), SW2.2, SW2.GND (SHIELD), SW3.2, SW4.1, U2.2 (GND), U3.4 (GND), U4.2 (ADDR), U4.7 (R), U4.8 (VSS), U4.9 (VSS), U5.6 (VSS), U5.7 (A0), U5.8 (A1), U5.9 (A2), U5.10 (A3), U5.17 (VSS_pad), U6.3 (GND), U6.4 (CSB_1), U7.8 (VSS), U8.14 (~CE), U8.15 (GND), U9.7 (GND), U10.4 (ADD), U10.18 (GND_1), U10.24 (GND_2), U10.26 (GND_3), U10.33 (CCRD_PRST), U10.35 (N.C._1), U10.36 (N.C._2), U10.37 (GND_4), U10.41 (GND_5), U11.6 (GND), U11.18 (GND), U11.28 (GND), U11.39 (GND), U12.8 (GND), U12.15 (~EN), U13.1 (A0), U13.2 (A1), U13.3 (A2), U13.4 (GND), U13.7 (WP), U14.5 (GND), U15.7 (GND), U16.7 (GND), U17.7 (GND), U18.5 (GND), U18.9, Y1.2, Y1.4, locked.19 (GND), locked.24 (AGND), locked.29 (THERMAL_PAD)
unnamed: BT1.1+ (+), F1.2
unnamed: BT1.1- (-), BT1.2- (-), BT2.1- (-), BT2.2- (-), BT2.3- (-), NT1.2, R31.1
unnamed: BT1.2+ (+), F2.2
unnamed: BT2.1+ (+), F3.2
unnamed: BT2.2+ (+), F4.2
unnamed: BT2.3+ (+), F5.2
unnamed: BZ1.2 (+), Q7.3 (C)
unnamed: D1.1 (K), R10.1
unnamed: D2.1 (K), R11.1
unnamed: D3.1 (K), R21.1
unnamed: D4.1 (K), R22.1
unnamed: D5.1 (K), R32.1
unnamed: D6.1 (K), R33.1
unnamed: D7.1 (K), R34.1
unnamed: D8.1 (K), R35.1
unnamed: D9.1 (K), R36.1
unnamed: D10.1 (K), R37.1
unnamed: D11.1 (K), R38.1
unnamed: D12.1 (K), R39.1
unnamed: D13.1 (K), R42.1
unnamed: D14.1 (K), R43.1
unnamed: D15.1 (K), R53.1
unnamed: J1.A5 (CC1), R4.2
unnamed: J1.B5 (CC2), R3.2
unnamed: J3.1 (CD/DAT3), R51.2
unnamed: J3.5 (CLK), R49.2
unnamed: J3.2 (CMD), R50.2
unnamed: J3.7 (DAT0), R48.1
unnamed: J3.8 (DAT1), R47.1
unnamed: J3.9 (DAT2), R52.2
unnamed: JP1.1 (A), R8.2
unnamed: L5.1, U18.7 (VOUT), U18.8 (VOUT)
unnamed: Q1.1 (B), R19.2
unnamed: Q1.3 (C), R21.2
unnamed: Q2.1 (B), R20.2
unnamed: Q2.3 (C), R22.2
unnamed: Q3.1 (B), R28.2
unnamed: Q3.3 (C), R29.2
unnamed: Q4.1 (B), R40.2
unnamed: Q4.3 (C), R42.2
unnamed: Q5.1 (B), R41.2
unnamed: Q5.3 (C), R43.2
unnamed: Q6.1 (B), R45.2
unnamed: Q6.3 (C), R53.2
unnamed: Q7.1 (B), R46.2
unnamed: R27.2, TH2.2
unnamed: R2.2, locked.4 (DCNF0)
unnamed: R1.2, locked.5 (DCNF1)
unnamed: R7.1, locked.20 (DM)
unnamed: R6.1, locked.21 (DP)
unnamed: R5.2, locked.26 (VBUS_DET)
unnamed: R16.1, TP1.1, U5.2 (~RESET)
unnamed: TH1.2, U7.11 (P6/TS)
unnamed: C15.1, TH1.1, U7.7 (REG25)
unnamed: C10.2, C14.1, R25.2, U7.10 (SRN)
unnamed: C10.1, C13.1, R24.2, U7.9 (SRP)
unnamed: C16.2, U8.1 (BTST)
unnamed: C11.1, R23.1, U8.4 (ILIM)
unnamed: C7.1, C8.1, U8.17 (PMID)
unnamed: C19.1, U8.2 (REGN)
unnamed: C16.1, L1.1, U8.16 (SW)
unnamed: R26.2, R27.1, TH2.1, U8.6 (TS)
unnamed: R26.1, U8.5 (TS_BIAS)
unnamed: R54.2, R55.1, U10.28 (KVBUS)
unnamed: C27.1, C31.1, U11.29 (AREF)
unnamed: C30.1, U11.8 (XTAL1), Y1.3
unnamed: C28.1, U11.7 (XTAL2), Y1.1
unnamed: U14.1 (OSCI), Y2.2
unnamed: U14.2 (OSCO), Y2.1
unnamed: C32.1, U14.3 (VBAT)
unnamed: L2.1, U15.3 (LX1)
unnamed: L2.2, U15.2 (LX2)
unnamed: L3.1, U16.3 (LX1)
unnamed: L3.2, U16.2 (LX2)
unnamed: L4.1, U17.3 (LX1)
unnamed: L4.2, U17.2 (LX2)
unnamed: C45.1, U18.6 (CT)
RST#: C29.2, R8.1
SCL_I2C: R18.1, U3.3 (SCLin), U4.4 (SCL), U5.11 (SCL_SLAVE), U6.8 (SCLK), U7.13 (P4/SCL), U8.13 (SCL), U10.2 (SCL), U13.6 (SCL), U14.7 (SCL)
SCL_MCU: R12.1, U5.1 (SCL_MST0), U11.19 ((PCINT16/SCL)PC0)
SDA_I2C: R17.1, U3.6 (SDAin), U4.1 (SDA), U5.12 (SDA_SLAVE), U6.7 (SDI/SDA), U7.14 (P3/SDA), U8.12 (SDA), U10.3 (SDA), U13.5 (SDA), U14.6 (SDA)
SDA_MCU: R13.1, U5.16 (SDA_MST0), U11.20 ((PCINT17/SDA)PC1)
USB_D+: U2.3 (I/O2), U10.22 (CD+)
USB_D-: U2.1 (I/O1), U10.21 (CD-)
USB_FTDI_D+: R6.2, U10.20 (HD+)
USB_FTDI_D-: R7.2, U10.19 (HD-)
VBUS: C3.1, J1.A4/B9 (VBUS), J1.B4/A9 (VBUS), R5.1, R54.1, U2.5 (VBUS), U8.18 (VBUS)

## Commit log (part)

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2023-10-18 initial commit, WIP
2023-10-19 wip: add new components, try to prepare layout outlines
2023-10-20 wip, update schematics, board outlines
2023-10-23 WIP: schematics and layout improvements
2023-10-25 wip layout, add datasheets
2023-10-26 WIP, layout improvement
2023-10-28 wip, layout progress
2023-10-28 wip, layout improvements
2023-10-28 wip: layout
2023-10-29 Wip, layout
2023-10-30 WIP, routing
2023-11-04 rename source files
2023-11-04 add assets
2023-11-04 Update metadata files
2023-11-04 wip, split power adapter to BATDATSOCKET01
2023-11-05 WIP, add ust ID for existing parts
2023-11-05 uprava schematu
2023-11-05 WIP, schematic improvements, bigger page, reststructualized
2023-11-05 Updates in schematics, improved readability
2023-11-05 minor updates, update kibot
2023-11-06 clean outputs
2023-11-06 resave project
2023-11-06 pokus: odebran vykonovy vypinac
2023-11-06 pokus: odstraneni skupin o kterych vim
2023-11-06 Update actions products
2023-11-06 update library
2023-11-06 Update workflow files
2023-11-06 updated power button connection
2023-11-06 allow to keep gauge powered up permanently
2023-11-06 Layout update, place and route new added components
2023-11-06 solve drc, fill ust_id
2023-11-06 update solder jumper to closed
2023-11-07 Add datasheet to RTC schematics symbol.
2023-11-07 fix absolute path to sheet template.
2023-11-07 Connect RTC interrupt pin to charge EXT_DETECTION_CHARGER.
2023-11-07 Update template path.
2023-11-07 Fix typo in title block.
2023-11-07 tune usb trace length, route RTC wakeup mode
2023-11-07 DTR jumper connected
2023-11-07 Zvetseni mezery od hrany PCB
2023-11-07 Improve layout - Remove copper pour antennas (add grounding vias) - Remove solder mask uncovered traces connections to pads
2023-11-07 oprava cesticky u +BATT
2023-11-07 Fix poorly connected vias.
2023-11-07 Resolve ERC errors.
2023-11-07 join gnd areas
2023-11-08 Replace absolute 3D model path with relative.
2023-11-14 repair known issues
2023-11-17 Remove manually generated schematics.
2023-11-18 Fix type of shift register to LEDs.
2023-11-18 Improve readability.
2023-11-19 change I2C switch footprint, change I2C address of MAX IC
2023-11-19 Improve readability of schematics.
2023-11-19 Fix typos in schematics.
2023-11-19 Add vias to improve switching power supply layout.
2023-11-19 Add a link to datasheet to SD card power switch.
2023-11-19 improvements in layout, add oscilator, update mode path, USB line impedance
2023-11-19 Rework of via placement after incomplete merge.
2023-11-20 minor updates in schematics
2023-11-20 Add power consumption notes to schematics.
2023-11-20 Create LICENSE
2023-11-26 Vylepseni, upravy layoutu, zmena ovladani ledky, reset pin do molex konektoru
2023-11-26 Update README.md
    Add image.
2023-11-27 add USB detect from FTDI to MCU
2023-11-27 add RTS, CTS
2023-11-28 Routing improvement.
2023-11-28 Resolve majority of DRC issues.
2023-11-28 Change oscillator footprint. WIP
2023-11-28 Routed Oscillator in 2.5x2 mm package.
2023-11-28 Add blocking capacitor to EEPROM.
2023-11-28 Updata littlefuse footprint to NANO02 fuse holder.
2023-11-28 Layout improvements.
2023-11-28 Change USB signal via to uVia.
2023-11-28 Move SD card reader oscillator away from USB data tracks and isolate it by GND strip.
2023-11-28 Swap button pins. Resolve #7
2023-11-28 Fix poor power connection under MCU.
2023-11-28 Connect the RTC time-stamp input to USER A button.
2023-11-29 Change diode D6 to decrease leakage current.
2023-11-29 Resolve silkscreen overlap.
2023-12-01 Improve schematics.
2023-12-06 Add note to correct. Orientation of LED bar indicator.
2023-12-06 Fix LED bar color indication and LED intensity.
2023-12-06 Fix title block and revision.
2023-12-08 add notes to LED currents.
2023-12-09 Move ground symbol.
2023-12-10 Update components values to tested ones.
2023-12-10 Fix UST_ID.
2023-12-10 Update and correct values from manufacturing process.
2023-12-15 Update the commponent values according to actual component values used during manufacturing.
2023-12-21 Update README.md
    Add a diagram of the internal connection.
2024-03-05 Update documentation.
2024-03-05 Update preview.
2024-03-05 Crop image.
2024-03-05 Update README.md
    Add a preview to the top of the readme.
2024-03-09 Adding photo of BATDATUNIT01 used in AIRDOS04.
2024-03-29 Update link to buzzer datasheet.
2024-07-18 Cleaning up.
2025-04-01 Improve automatic power up reliability by changing power up circuit components values.
2025-04-27 Silkscreen improvement.
2025-05-10 Convert to KiCAD 9 Add CR2032 battery holder to avoid RTC reset with removed accumulators.
2025-05-12 Update project wokflows to KiCAD 9.
2025-05-14 Resolve #11 Improve silkscreen Fix DRC errors.
2025-05-14 Resolve #10 Updating battery holder silkscreen.
2025-05-14 Resolve #8 Mirror symbol vertically in schematic.
2025-05-14 Resolve #9 Change footprint pads to rectangular.
2025-05-14 Revert "Update workflow files"
    This reverts commit a76b4aa6289d3fc5a08ea91524d34dd0d68b47b0.
2025-05-14 Revert wrong automatic update of workflows.
2025-05-14 Switch branch of assets submodule to KiCADv9.
2025-05-14 Update UST_IDs.
2025-05-14 Repair white characters in UST_ID fields.
2025-05-14 Fix attributes of some components.
2025-09-10 Make schematics more clean.
2025-11-25 Update schematics symbols.
2025-11-25 Update ATmega symbol.
2025-11-25 Improve schematic layout.
2026-02-07 Cleanup schematics.
2026-04-27 Add datasheet for RTC chip.
